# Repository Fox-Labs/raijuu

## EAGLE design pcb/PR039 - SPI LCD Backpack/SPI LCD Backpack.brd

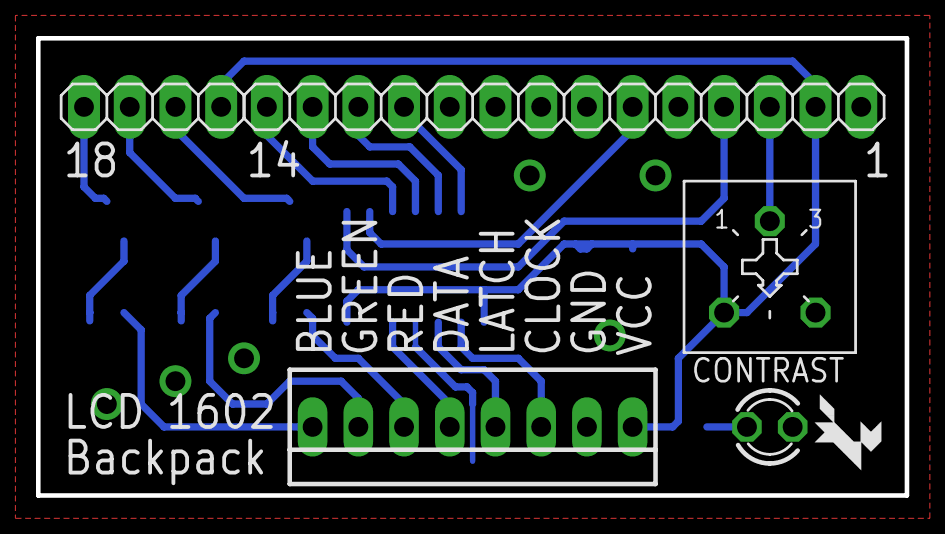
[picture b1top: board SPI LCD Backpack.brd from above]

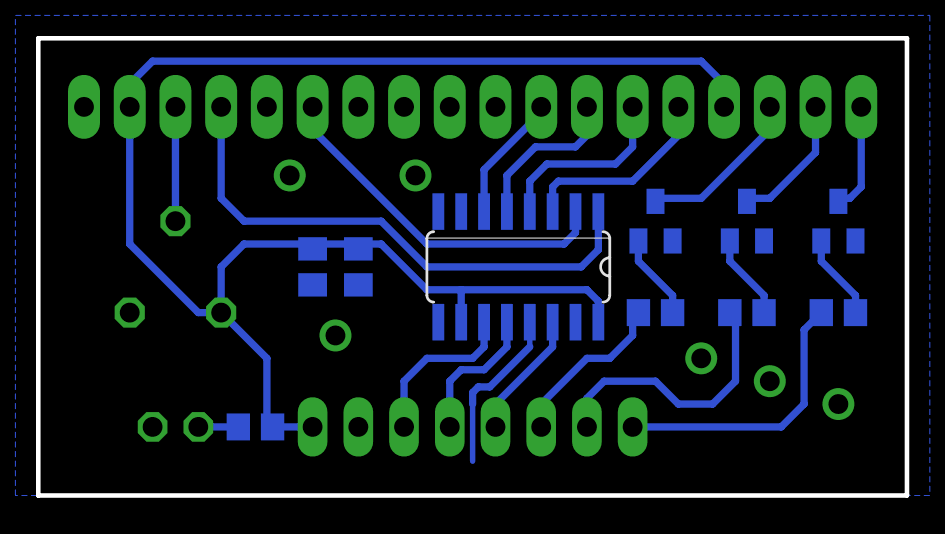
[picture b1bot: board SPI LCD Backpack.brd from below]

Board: 2 copper layers, 48.3 x 25.4 mm, 16 parts (10 on the bottom side), 22 nets.

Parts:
C1: 1uF; C0805K
C2: 100nF; C0805K
IC1: 74HC595D; SO16
JP1: 1X14
JP2: 1X04
LED1: LED3MM
R1: 1k; R0805
R2: 3386F
R3, R4, R5: 10k; R0805
T1, T2, T3: BC847; SOT23
U$1: FOX-1
X1: 22-23-2081

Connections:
+5V: C1.1, C2.1, IC1.10, IC1.16, JP1.2, JP2.1, R1.2, R2.1, X1.1
BLUE: R5.1, X1.8
CLOCK: IC1.11, X1.3
DATA: IC1.14, X1.5
DB4: IC1.6, JP1.11
DB5: IC1.5, JP1.12
DB6: IC1.4, JP1.13
DB7: IC1.3, JP1.14
E: IC1.2, JP1.6
GND: C1.2, C2.2, IC1.8, IC1.13, JP1.1, JP1.5, LED1.K, R2.3, T1.2, T2.2, T3.2, X1.2
GREEN: R4.1, X1.7
LATCH: IC1.12, X1.4
unnamed: R3.2, T1.1
unnamed: R4.2, T2.1
unnamed: R5.2, T3.1
unnamed: LED1.A, R1.1
unnamed: JP1.3, R2.2
unnamed: JP2.2, T1.3
unnamed: JP2.3, T2.3
unnamed: JP2.4, T3.3
RED: R3.1, X1.6
RS: IC1.1, JP1.4

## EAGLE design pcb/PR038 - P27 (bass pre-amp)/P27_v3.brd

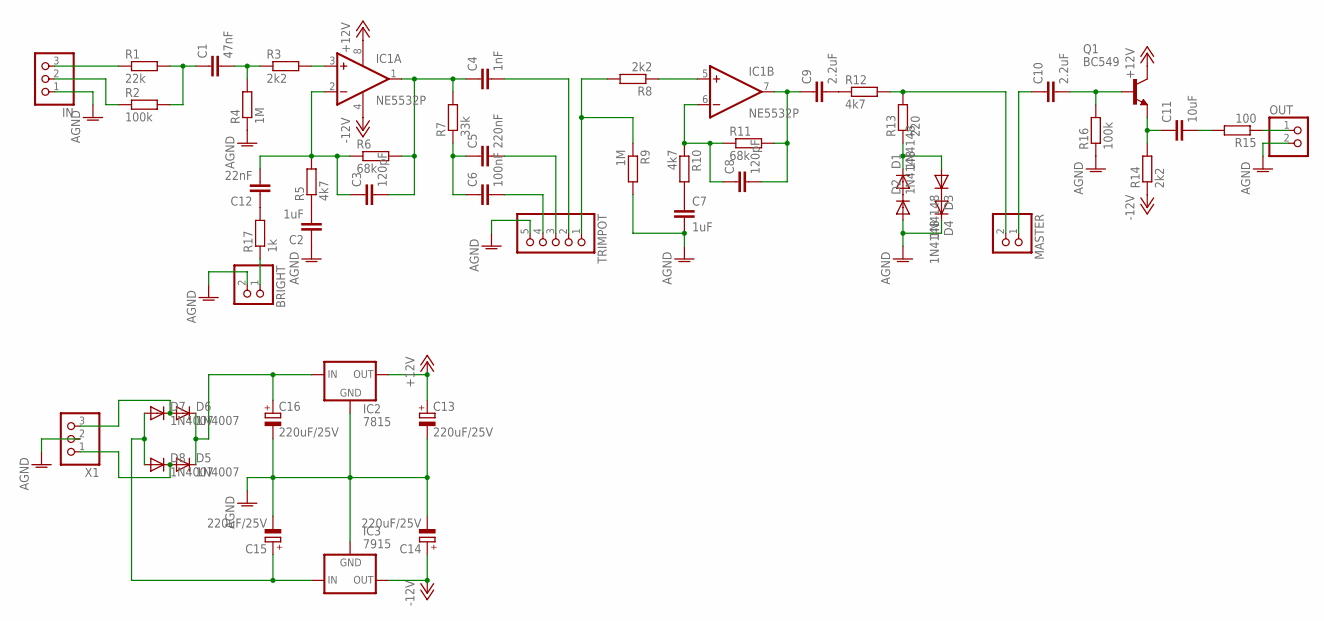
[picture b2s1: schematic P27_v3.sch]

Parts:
BRIGHT: PINHD-1X2; 1X02
C1: 47nF; C050-025X075
C2, C7: 1uF; C050-025X075
C3, C8: 120pF; C050-025X075
C4: 1nF; C050-025X075
C5: 220nF; C050-025X075
C6: 100nF; C050-025X075
C9, C10: 2.2uF; C050-025X075
C11: 10uF; C050-025X075
C12: 22nF; C050-025X075
C13, C14, C15, C16: 220uF/25V; E2,5-6
D1, D2, D3, D4: 1N4148; DO41-7
D5, D6, D7, D8: 1N4007; DO41-7
IC1: NE5532P; DIL08
IC2: 7815; 78XXS
IC3: 7915; 79XXS
IN: PINHD-1X3180; 1X03
MASTER: PINHD-1X2; 1X02
OUT: PINHD-1X2; 1X02
Q1: BC549; TO92
R1: 22k; 0207/7
R2, R16: 100k; 0207/7
R3, R8, R14: 2k2; 0207/7
R4, R9: 1M; 0207/7
R5, R10, R12: 4k7; 0207/7
R6, R11: 68k; 0207/7
R7: 33k; 0207/7
R13: 220; 0207/7
R15: 100; 0207/7
R17: 1k; 0207/7
TRIMPOT: PINHD-1X5; 1X05
X1: W237-103

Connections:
+12V: C13.+, IC1.8 (V+), IC2.OUT, Q1.3 (C)
-12V: C14.+, IC1.4 (V-), IC3.OUT, R14.1
AGND: BRIGHT.2, C2.1, C7.2, C13.-, C14.-, C15.-, C16.-, D2.A, D4.C, IC2.GND, IC3.GND, IN.1, OUT.2, R4.1, R9.2, R16.1, TRIMPOT.5, X1.2
BAS: C5.2, TRIMPOT.3
HI: IN.3, R1.1
IN: C10.1, MASTER.1
LOW: IN.2, R2.1
MID: C6.2, TRIMPOT.4
unnamed: C1.1, R1.2, R2.2
unnamed: IC1.3 (+IN), R3.2
unnamed: C1.2, R3.1, R4.2
unnamed: C3.1, C12.2, IC1.2 (-IN), R5.2, R6.1
unnamed: C2.2, R5.1
unnamed: C3.2, C4.1, IC1.1 (OUT), R6.2, R7.2
unnamed: C5.1, C6.1, R7.1
unnamed: C10.2, Q1.2 (B), R16.2
unnamed: C7.1, R10.2
unnamed: IC1.5 (+IN), R8.1
unnamed: C11.1, Q1.1 (E), R14.2
unnamed: C11.2, R15.2
unnamed: C8.1, IC1.6 (-IN), R10.1, R11.1
unnamed: C8.2, C9.1, IC1.7 (OUT), R11.2
unnamed: OUT.1, R15.1
unnamed: C9.2, R12.1
unnamed: D1.A, D2.C
unnamed: D3.C, D4.A
unnamed: D1.C, D3.A, R13.1
unnamed: D6.A, D7.C, X1.3
unnamed: C12.1, R17.2
unnamed: BRIGHT.1, R17.1
unnamed: D5.A, D8.C, X1.1
unnamed: C16.+, D5.C, D6.C, IC2.IN
unnamed: C15.+, D7.A, D8.A, IC3.IN
OUT: MASTER.2, R12.2, R13.2
TRB: C4.2, TRIMPOT.2
VOL: R8.2, R9.1, TRIMPOT.1

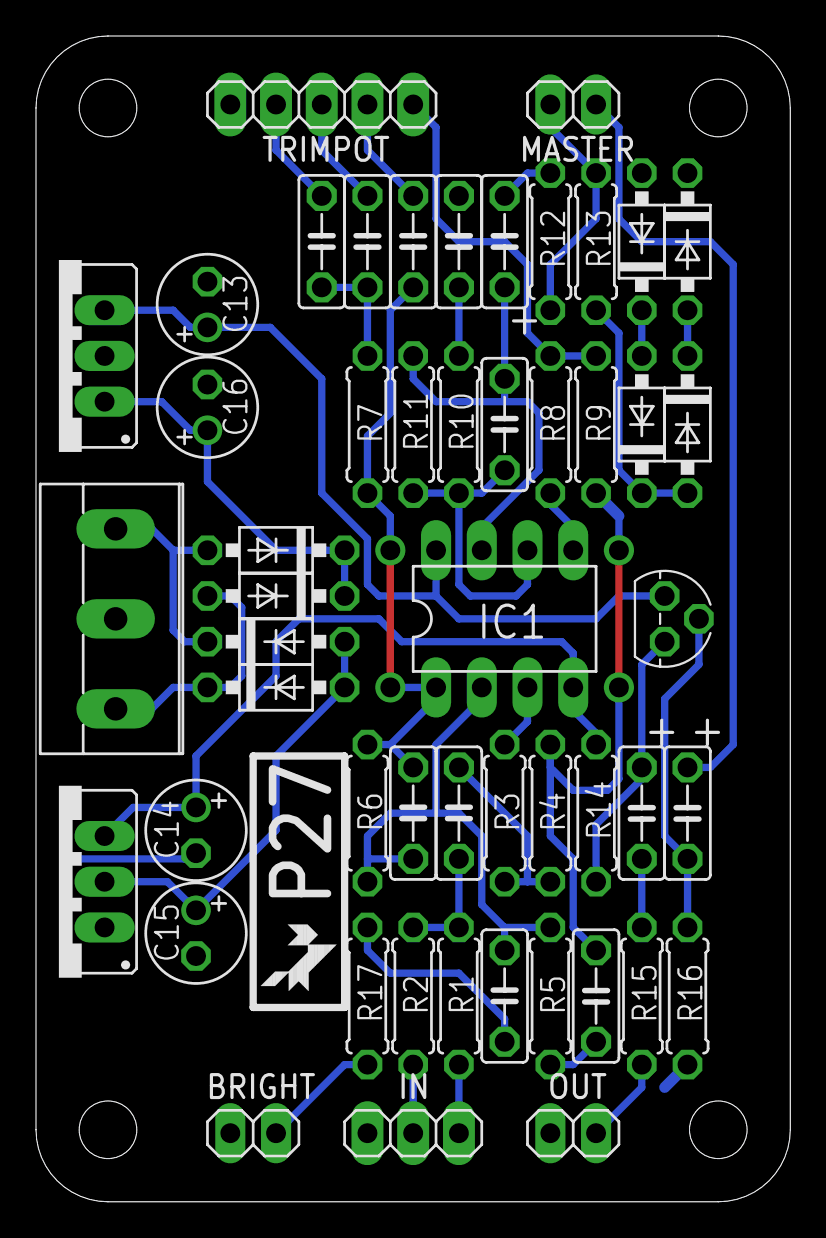
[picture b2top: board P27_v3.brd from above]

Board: 2 copper layers, 41.9 x 64.8 mm, 52 parts (0 on the bottom side), 36 nets.

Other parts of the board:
U$1: FOX-1

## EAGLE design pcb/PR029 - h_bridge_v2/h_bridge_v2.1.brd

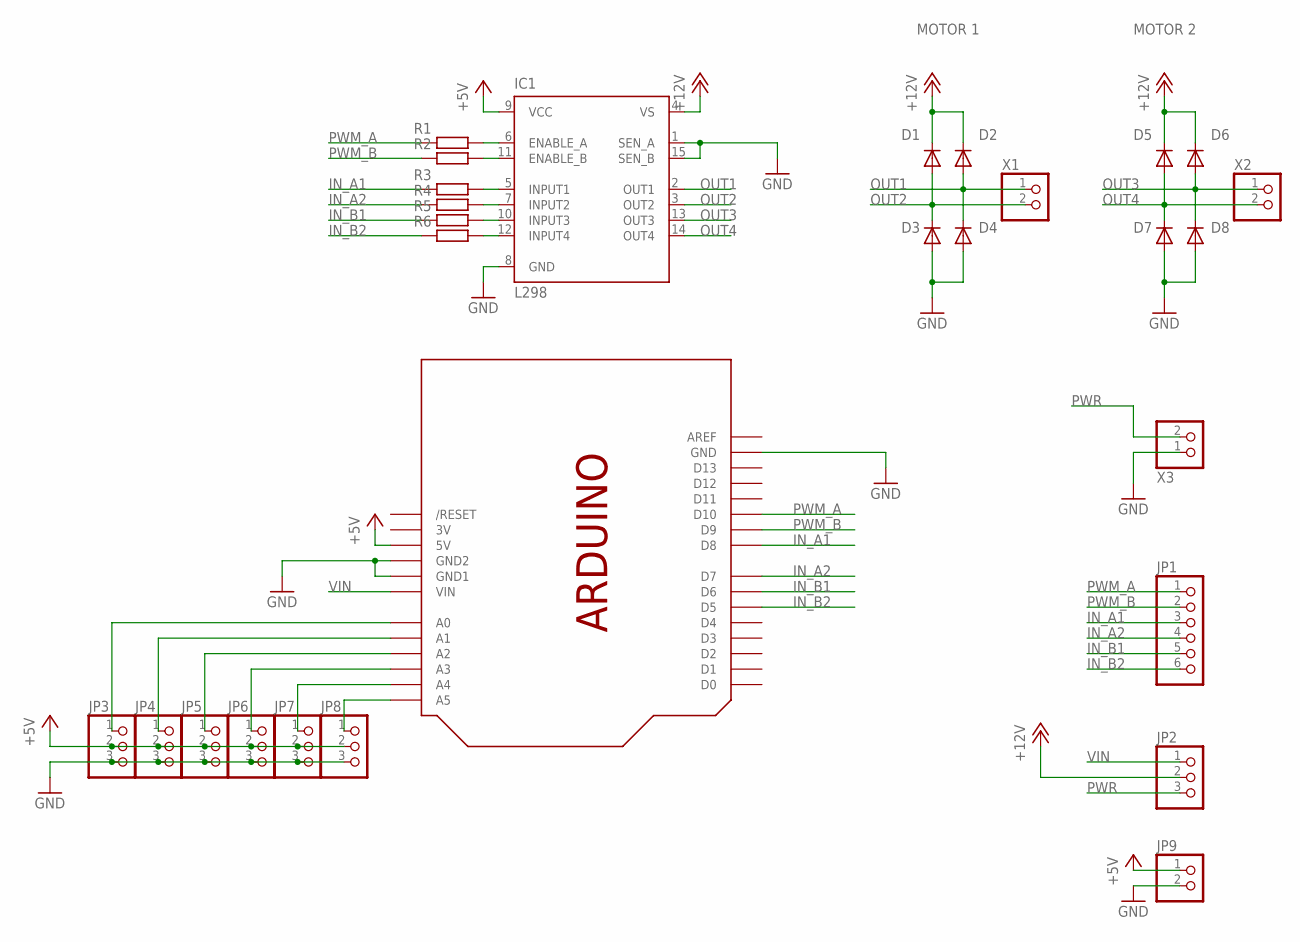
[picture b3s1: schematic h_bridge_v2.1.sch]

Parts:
D1, D2, D3, D4, D5, D6, D7, D8: 1N4004A; DO41-10
IC1: L298; MULTIWATT-15
JP1: PINHD-1X6; 1X06
JP2, JP3, JP4, JP5, JP6, JP7, JP8: PINHD-1X3180; 1X03
JP9: PINHD-1X2; 1X02
R1, R2, R3, R4, R5, R6: R-EU_0207/10; 0207/10
U$1: ARDUINO-HOLE
X1, X2, X3: W237-102

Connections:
3V: U$1.3V
+5V: IC1.9 (VCC), JP3.2, JP4.2, JP5.2, JP6.2, JP7.2, JP8.2, JP9.1, U$1.5V
+12V: D1.C, D2.C, D5.C, D6.C, IC1.4 (VS), JP2.2
GND: D3.A, D4.A, D7.A, D8.A, IC1.1 (SEN_A), IC1.8 (GND), IC1.15 (SEN_B), JP3.3, JP4.3, JP5.3, JP6.3, JP7.3, JP8.3, JP9.2, U$1.GND, U$1.GND1, U$1.GND2, X3.1
IN_A1: JP1.3, R3.1, U$1.D8
IN_A2: JP1.4, R4.1, U$1.D7
IN_B1: JP1.5, R5.1, U$1.D6
IN_B2: JP1.6, R6.1, U$1.D5
unnamed: IC1.6 (ENABLE_A), R1.2
unnamed: IC1.11 (ENABLE_B), R2.2
unnamed: IC1.5 (INPUT1), R3.2
unnamed: IC1.7 (INPUT2), R4.2
unnamed: IC1.10 (INPUT3), R5.2
unnamed: IC1.12 (INPUT4), R6.2
unnamed: JP3.1, U$1.A0
unnamed: JP4.1, U$1.A1
unnamed: JP5.1, U$1.A2
unnamed: JP6.1, U$1.A3
unnamed: JP7.1, U$1.A4
unnamed: JP8.1, U$1.A5
OUT1: D2.A, D4.C, IC1.2 (OUT1), X1.1
OUT2: D1.A, D3.C, IC1.3 (OUT2), X1.2
OUT3: D6.A, D8.C, IC1.13 (OUT3), X2.1
OUT4: D5.A, D7.C, IC1.14 (OUT4), X2.2
PWM_A: JP1.1, R1.1, U$1.D10
PWM_B: JP1.2, R2.1, U$1.D9
PWR: JP2.3, X3.2
VIN: JP2.1, U$1.VIN

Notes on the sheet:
MOTOR 1
MOTOR 2

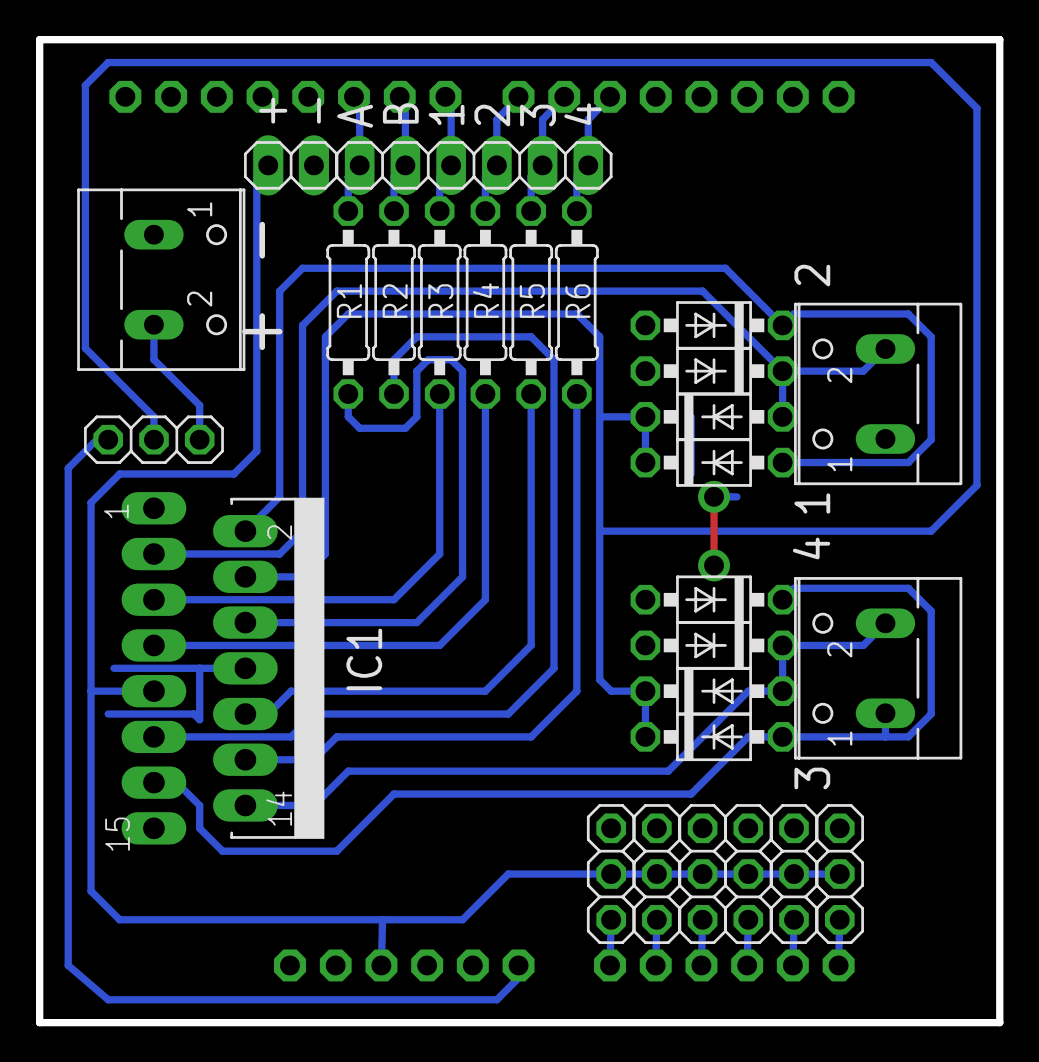
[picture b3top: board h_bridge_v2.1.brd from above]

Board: 2 copper layers, 53.3 x 54.6 mm, 28 parts (0 on the bottom side), 27 nets.

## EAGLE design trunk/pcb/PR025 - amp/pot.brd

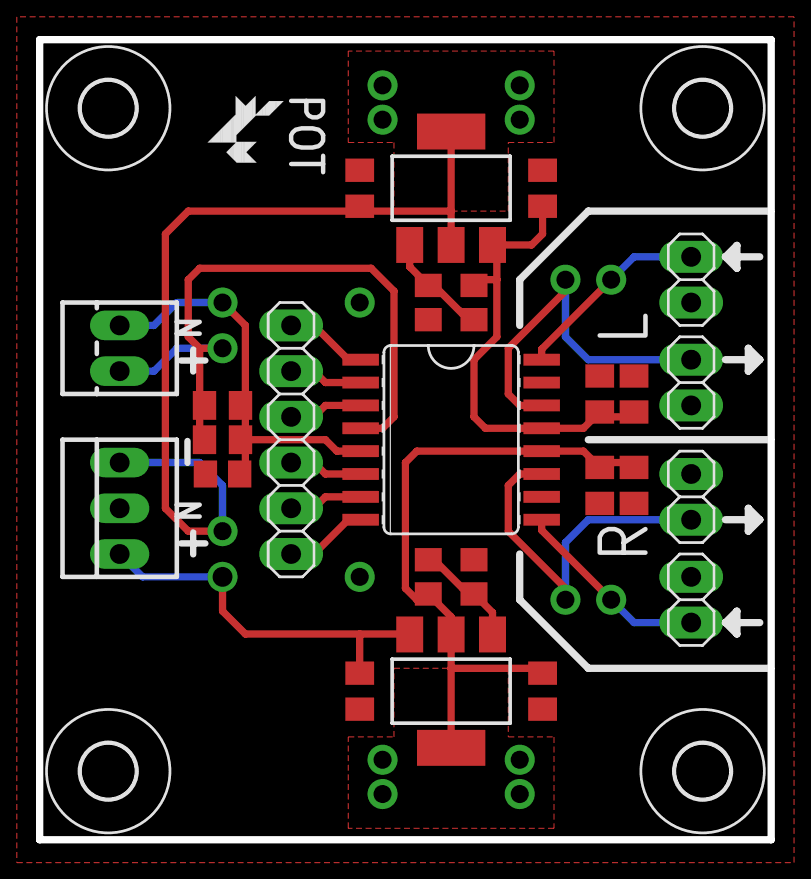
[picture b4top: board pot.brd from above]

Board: 2 copper layers, 40.6 x 44.4 mm, 30 parts (0 on the bottom side), 19 nets.

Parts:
C1, C2: 1uF; C0805K
C3, C4, C6, C8, C9: 10uF; C0805K
C5, C7, C10: 100nF; C0805K
IC1: LM317; SOT223
IC2: LM337; SOT223
JP1: 1X06
JP2, JP3, JP4, JP5: 1X02
R1, R2: 680; R0805
R3, R4: 220; R0805
R5: 0; R0805
U1: PGA2311; SO16W
U$1, U$2, U$3, U$4: 3,0
U$5: FOX-1
X1: 22-23-2031
X2: 22-23-2021

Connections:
+5V: C3.1, C5.1, C6.1, IC1.2, IC1.4, R3.2, U1.12
+12V: C1.1, IC1.3, X1.1
-5V: C4.1, C7.1, C8.1, IC2.3, R4.1, U1.13
-12V: C2.1, IC2.2, IC2.4, X1.3
/CS: JP1.2, U1.2
/MUTE: JP1.6, U1.8
AGND: C1.2, C2.2, C3.2, C4.2, C5.2, C6.2, C7.2, C8.2, JP2.2, JP3.2, JP4.2, JP5.2, R1.1, R2.2, R5.1, U1.10, U1.15, X1.2
GND: C9.2, C10.2, R5.2, U1.5, X2.2
IN_L: JP3.1, U1.16
IN_R: JP2.1, U1.9
unnamed: IC2.1, R2.1, R4.2
unnamed: IC1.1, R1.2, R3.1
OUT_L: JP5.1, U1.14
OUT_R: JP4.1, U1.11
SCLK: JP1.4, U1.6
SDI: JP1.3, U1.3
SDO: JP1.5, U1.7
VCC: C9.1, C10.1, U1.4, X2.1
ZCEN: JP1.1, U1.1

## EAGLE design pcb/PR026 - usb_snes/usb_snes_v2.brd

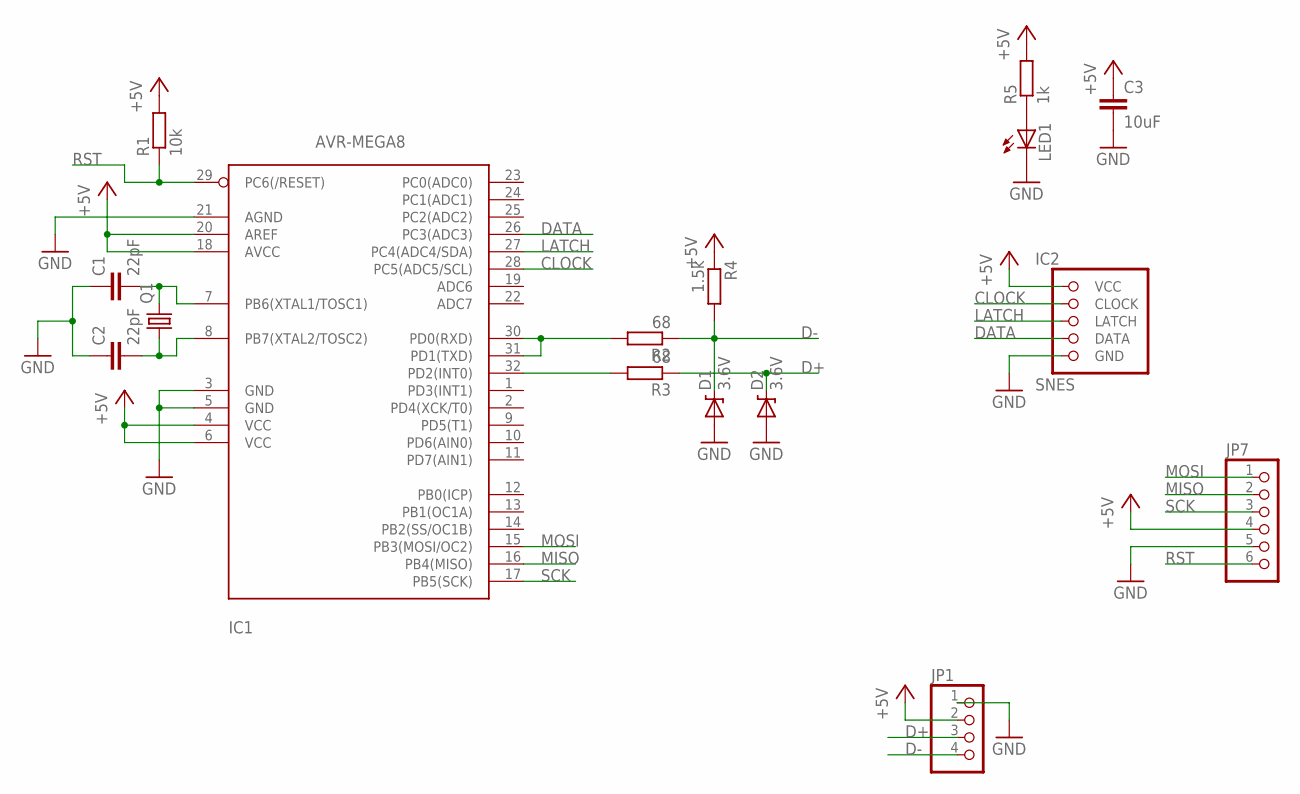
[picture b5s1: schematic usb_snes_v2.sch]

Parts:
C1, C2: 22pF; R0805
C3: 10uF; R0805
D1, D2: 3.6V; SOD123FL
IC1: AVR-MEGA8; TQFP32-08
IC2: SNES
JP1: PINHD-1X4S; 1X04-2MM
JP7: PINHD-1X6S; 1X06-2MM
LED1: LED0805; CHIP-LED0805
Q1: CRYSTALHC49UP; HC49UP
R1: 10k; R0805
R2, R3: 68; R0805
R4: 1.5k; R0805
R5: 1k; R0805

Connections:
+5V: C3.1, IC1.4 (VCC), IC1.6 (VCC), IC1.18 (AVCC), IC1.20 (AREF), IC2.5 (VCC), JP1.2, JP7.4, R1.2, R4.1, R5.2
CLOCK: IC1.28 (PC5(ADC5/SCL)), IC2.4 (CLOCK)
D+: D2.C, JP1.3, R3.1
D-: D1.C, JP1.4, R2.1, R4.2
DATA: IC1.26 (PC3(ADC3)), IC2.2 (DATA)
GND: C1.1, C2.1, C3.2, D1.A, D2.A, IC1.3 (GND), IC1.5 (GND), IC1.21 (AGND), IC2.1 (GND), JP1.1, JP7.5, LED1.C
LATCH: IC1.27 (PC4(ADC4/SDA)), IC2.3 (LATCH)
MISO: IC1.16 (PB4(MISO)), JP7.2
MOSI: IC1.15 (PB3(MOSI/OC2)), JP7.1
unnamed: C2.2, IC1.8 (PB7(XTAL2/TOSC2)), Q1.1
unnamed: C1.2, IC1.7 (PB6(XTAL1/TOSC1)), Q1.2
unnamed: IC1.30 (PD0(RXD)), IC1.31 (PD1(TXD)), R2.2
unnamed: IC1.32 (PD2(INT0)), R3.2
unnamed: LED1.A, R5.1
RST: IC1.29 (PC6(/RESET)), JP7.6, R1.1
SCK: IC1.17 (PB5(SCK)), JP7.3

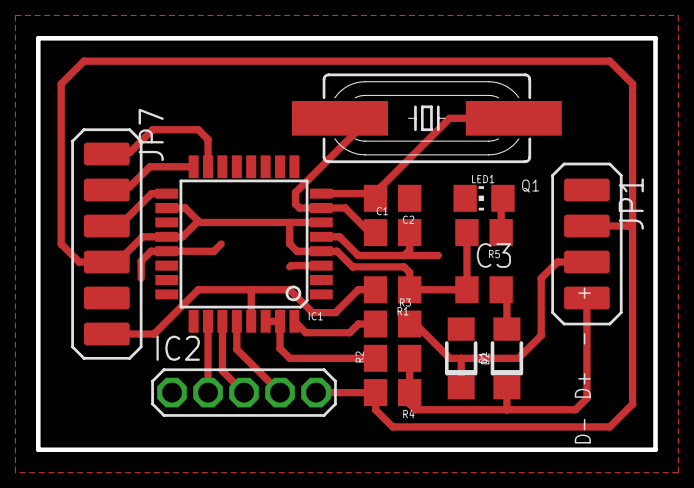
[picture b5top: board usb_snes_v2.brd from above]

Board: 2 copper layers, 34.3 x 22.9 mm, 16 parts (0 on the bottom side), 16 nets.

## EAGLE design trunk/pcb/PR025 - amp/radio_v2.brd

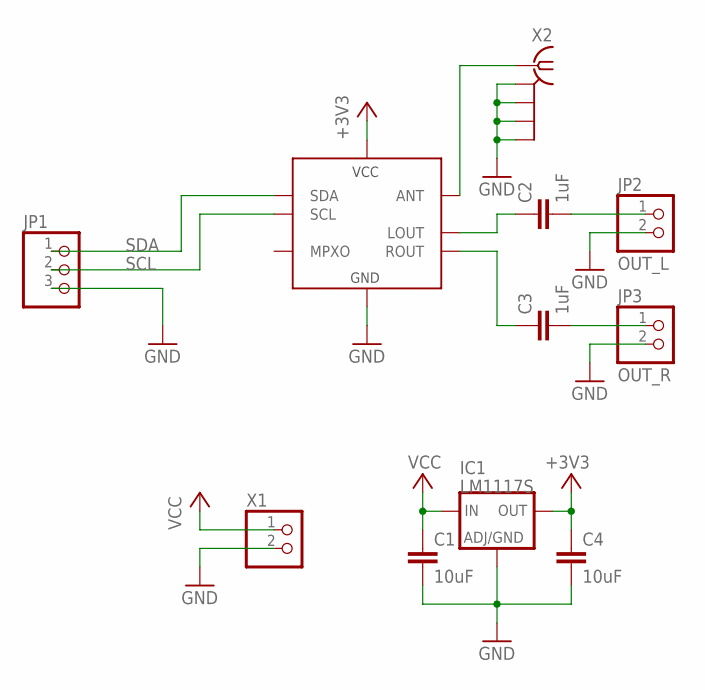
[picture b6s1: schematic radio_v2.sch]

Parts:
C1, C4: 10uF; C0805K
C2, C3: 1uF; C0805K
IC1: LM1117S; SOT223
JP1: PINHD-1X3180; 1X03
JP2: OUT_L; 1X02
JP3: OUT_R; 1X02
U1: TEA5767
X1: 22-23-2021
X2: BU-SMA-V

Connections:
+3V3: C4.1, IC1.2 (OUT), IC1.4 (OUT), U1.5 (VCC)
GND: C1.2, C4.2, IC1.1 (ADJ), JP1.3, JP2.2, JP3.2, U1.3 (GND), U1.6 (GND), X1.2, X2.2 (GND1), X2.3 (GND2), X2.4 (GND3), X2.5 (GND4)
unnamed: U1.10 (ANT), X2.1
unnamed: C3.1, U1.7 (ROUT)
unnamed: C3.2, JP3.1
unnamed: C2.2, JP2.1
OUT_R: C2.1, U1.8 (LOUT)
SCL: JP1.2, U1.2 (SCL)
SDA: JP1.1, U1.1 (SDA)
VCC: C1.1, IC1.3 (IN), X1.1

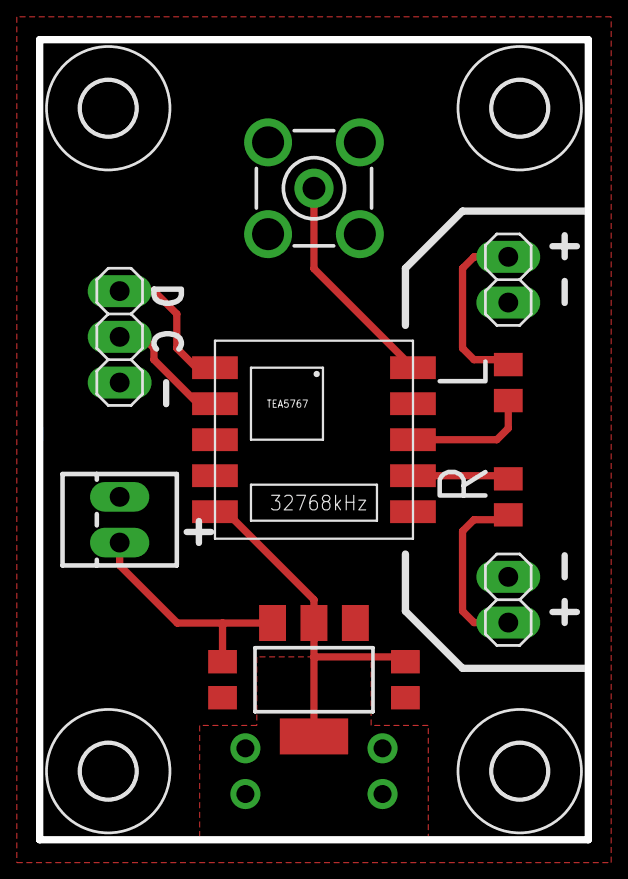
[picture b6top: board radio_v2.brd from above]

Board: 2 copper layers, 30.5 x 44.5 mm, 15 parts (0 on the bottom side), 10 nets.

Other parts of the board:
U$1, U$2, U$3, U$4: 3,0

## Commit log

2010-10-30 Created wiki page through web user interface.
2010-10-31 Praticamente todo o meu codigo...
2010-11-05 Update do transceptor, pinagem diferente e led RGB piscando...
2010-11-09 Atualizando o RF-24G, led muda o brilho e algumas mudanças no endereço presente na biblioteca.
2010-11-28 Implantado o sistema de cor no programa do transceptor.
    Rxx; muda o vermelho
    Gxx; muda o verde
    Bxx; muda o azul
    xx sendo um valor de 0 a 255 em hexadecimal
2011-04-03 Boards,boards,and more boards...
2011-04-05 Some small changes on pcb/usb_snes
2015-03-22 Migrating wiki contents from Google Code
2015-05-10 - Removed the modules of the amp system Moved then to another repository "https://github.com/MarceloPesse/BlueBox-PrototypeModules"
